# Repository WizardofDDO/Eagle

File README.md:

Eagle
=====

Projects created using Eagle 6.5.0

I was inspired to see if I could create the driver circuit for an RGB LED cube as seen on
Ytube so I downloaded Eagle 6.5.0 and got started. The method explained in the vidio seemed 
way too complicated for my taste so I put my brain to work and came up with the 8x8x8 version.
Next, I attempted to expand it to 16x16x16. Note, the latter is not finished and probably never
will be. It lacks power and ground as well as other things but its a good starting place for
anyone interested in finishing it. Dispite my joy at having a REAL electronics CAD program
I found some things just easier to do in paint, thus the gif files. Enjoy; The Wizard

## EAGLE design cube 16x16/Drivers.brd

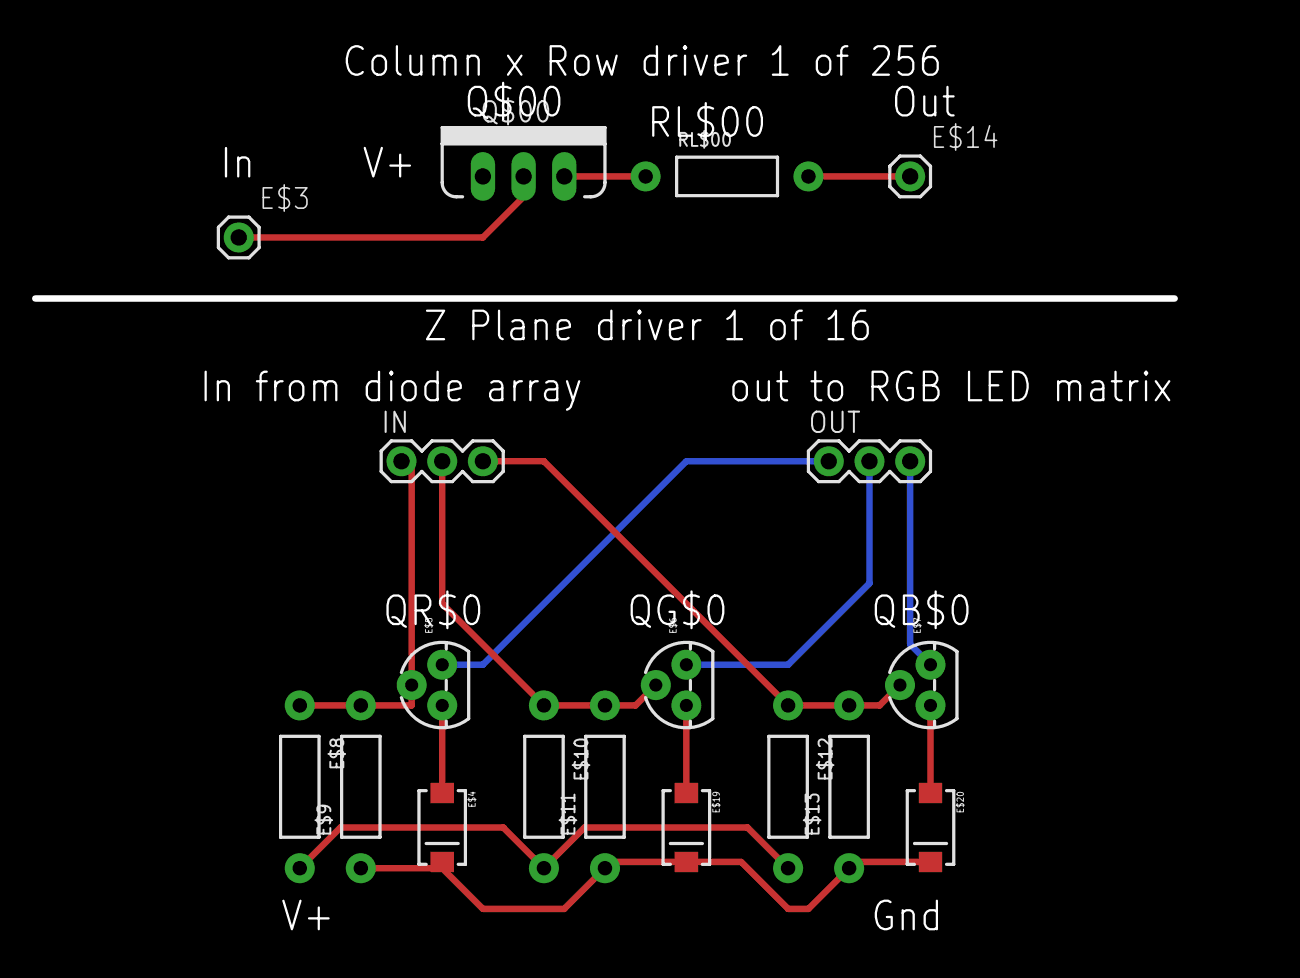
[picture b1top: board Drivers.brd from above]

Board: 2 copper layers, 76.7 x 56.7 mm, 18 parts (0 on the bottom side), 14 nets.

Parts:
E$3, E$14: 1X01
E$4, E$19, E$20: SMA-DIODE
E$5, E$6, E$7: TO-92
E$8, E$9, E$10, E$11, E$12, E$13: AXIAL-0.4
IN: R G B; 1X03
OUT: R G B; 1X03
Q$00: TO220V
RL$00: AXIAL-0.4

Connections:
S$1: E$5.2, E$8.P$1, E$9.P$2, IN.1
S$2: E$6.2, E$10.P$1, E$11.P$2, IN.2
S$3: E$7.2, E$12.P$1, E$13.P$2, IN.3
S$4: E$5.3, OUT.1
S$5: E$6.3, OUT.2
S$6: E$7.3, OUT.3
S$7: E$7.1, E$20.A
S$8: E$8.P$2, E$10.P$2, E$12.P$2
S$9: E$6.1, E$19.A
S$10: E$3.1, Q$00.2
S$11: E$4.A, E$5.1
S$12: E$4.C, E$9.P$1, E$11.P$1, E$13.P$1, E$19.C, E$20.C
S$13: Q$00.3, RL$00.P$1
S$14: E$14.1, RL$00.P$2

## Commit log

2013-10-12 Led cube using Arduino's
2013-10-12 SORRY fixed a couple of typo's
2013-10-12 Analog schematic
2013-10-13 added board layout for drivers

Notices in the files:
parts and their libraries:
SparkFun-DiscreteSemi: Licensing: CC v3.0 Share-Alike You are welcome to use this library for commercial purposes.
